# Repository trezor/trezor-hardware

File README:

Hardware design of TREZOR

https://trezor.io/

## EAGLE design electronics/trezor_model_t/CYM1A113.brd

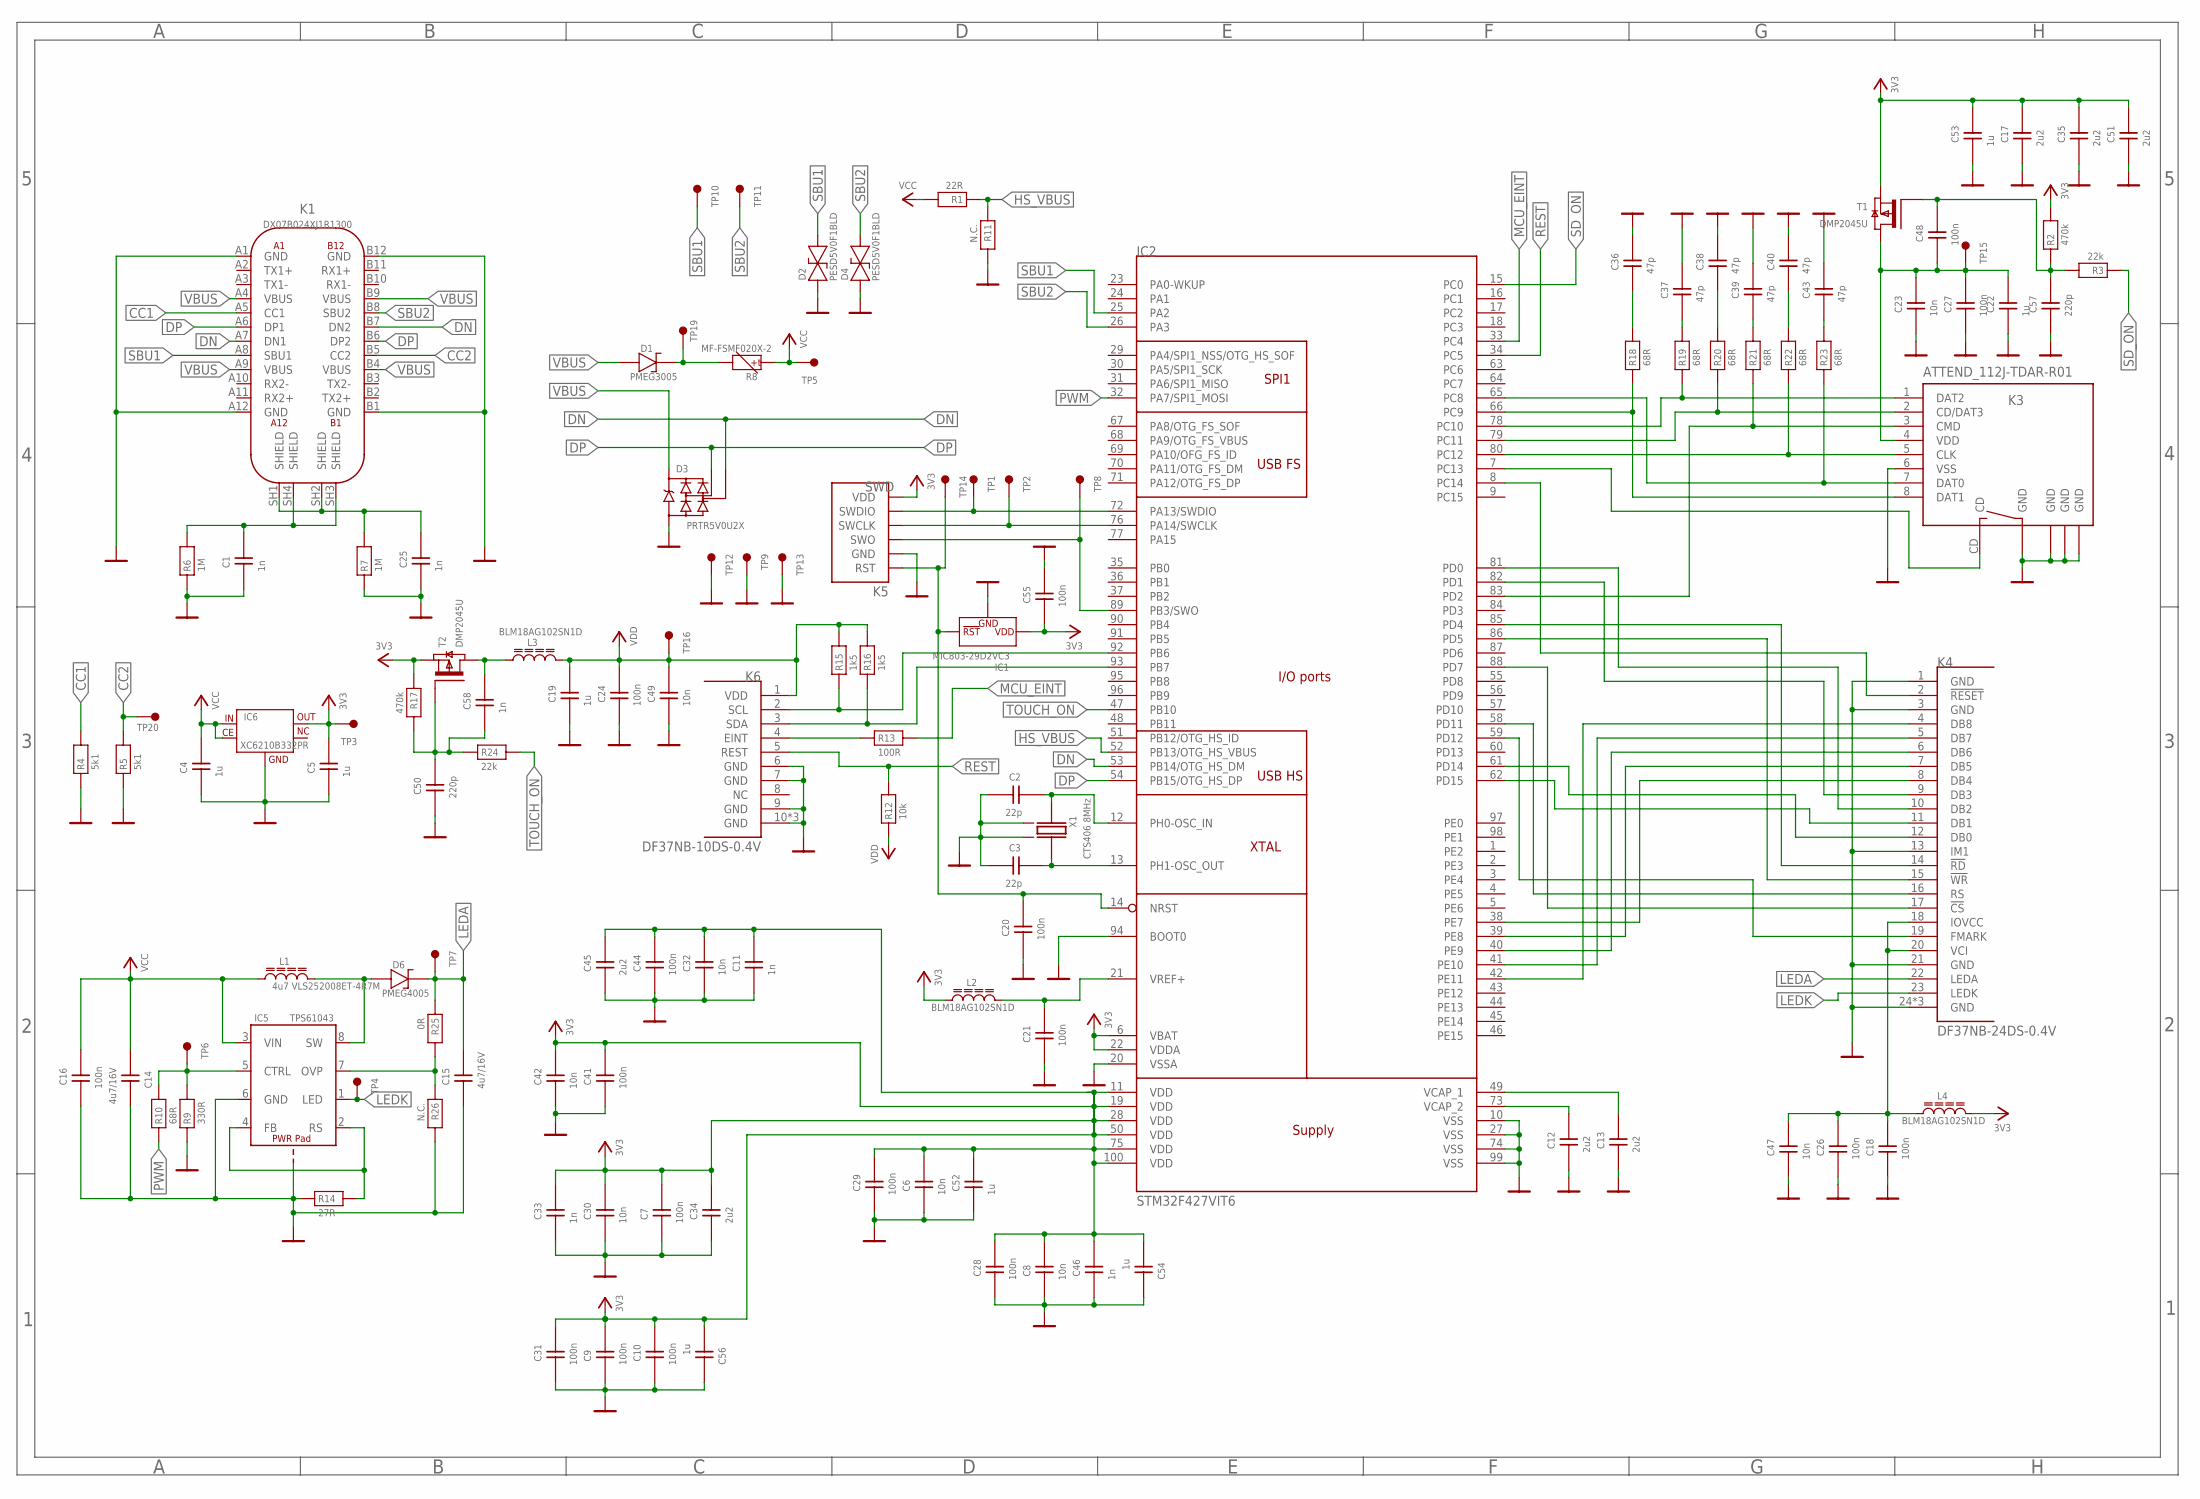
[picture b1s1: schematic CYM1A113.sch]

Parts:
C1, C11, C25, C33, C46, C58: 1n; 0402
C2, C3: 22p; 0402
C4, C19, C22, C52, C53, C54, C56: 1u; 0603_REFLOW
C5: 1u; 0603
C6, C8, C23, C30, C32, C42, C47, C49: 10n; 0402
C7, C9, C10, C16, C18, C20, C21, C24, C26, C27, C28, C29, C31, C41, C44, C48, C55: 100n; 0402
C12, C13, C17, C34, C35, C45, C51: 2u2; 0805_REFLOW
C14, C15: 4u7/16V; 0805_REFLOW
C36, C37, C38, C39, C40, C43: 47p; 0402
C50, C57: 220p; 0402
D1: PMEG3005; SOD323F
D2, D4: PESD5V0F1BLD; SOD882D
D3: PRTR5V0U2X; SOT143B_REFLOW
D6: PMEG4005; SOD323F
IC1: MIC803-29D2VC3; SOT23_MEDIUM_SIZE
IC2: STM32F427VIT6; LQFP100_NO_CENTER_NO_TDOCU
IC5: TPS61043; WSON-8_3X3MM
IC6: XC6210B332PR; SOT89-5
K1: DX07B024XJ1R1300; USB_C_JAE_DX07B024XJ1
K3: ATTEND_112J-TDAR-R01; ATTEND_112J-TXAR-R01_SMALL
K4: DF37NB-24DS-0.4V
K5: SWD
K6: DF37NB-10DS-0.4V
L1: 4u7 VLS252008ET-4R7M; L_2.5X2.0
L2, L3, L4: BLM18AG102SN1D; 0603_REFLOW
R1: 22R; 0402
R2, R17: 470k; 0402
R3, R24: 22k; 0402
R4, R5: 5k1; 0402
R6, R7: 1M; 0402
R8: MF-FSMF020X-2; 0603
R9: 330R; 0402
R10, R18, R19, R20, R21, R22, R23: 68R; 0402
R11, R26: N.C.; 0402
R12: 10k; 0402
R13: 100R; 0402
R14: 27R; 0402
R15, R16: 1k5; 0402
R25: 0R; 0402
T1, T2: DMP2045U; SOT23_REFLOW
TP1, TP2, TP4, TP6, TP7, TP8, TP9, TP12, TP13, TP14, TP15, TP16: MB_1.27; MB1.27
TP3, TP5, TP10, TP11: MB_1.50; MB1.5
TP19, TP20: MB_1.00
X1: CTS406 8MHz; X6,0X3,5

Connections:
CC1: K1.A5 (CC1), R4.P$2 (2)
CC2: K1.B5 (CC2), R5.P$2 (2), TP20.1
CTRL: IC5.5 (CTRL), R9.P$2 (2), R10.P$2 (2), TP6.1
DISP_!CS: IC2.88 (PD7), K4.17 (!CS)
DISP_!RD: IC2.85 (PD4), K4.14 (!RD)
DISP_!RESET: IC2.8 (PC14), K4.2 (!RESET)
DISP_!WR: IC2.86 (PD5), K4.15 (!WR)
DISP_DB0: IC2.61 (PD14), K4.12 (DB0)
DISP_DB1: IC2.62 (PD15), K4.11 (DB1)
DISP_DB2: IC2.81 (PD0), K4.10 (DB2)
DISP_DB3: IC2.82 (PD1), K4.9 (DB3)
DISP_DB4: IC2.38 (PE7), K4.8 (DB4)
DISP_DB5: IC2.39 (PE8), K4.7 (DB5)
DISP_DB6: IC2.40 (PE9), K4.6 (DB6)
DISP_DB7: IC2.41 (PE10), K4.5 (DB7)
DISP_DB8: IC2.42 (PE11), K4.4 (DB8)
DISP_FMARK: IC2.59 (PD12), K4.19 (FMARK)
DISP_RS: IC2.58 (PD11), K4.16 (RS)
DISP_VCC: C18.P$2 (2), C26.P$2 (2), C47.P$2 (2), K4.18 (IOVCC), K4.20 (VCI), L4.1
DN: D3.3 (I/O2), IC2.53 (PB14/OTG_HS_DM), K1.A7 (DN1), K1.B7 (DN2)
DP: D3.2 (I/O1), IC2.54 (PB15/OTG_HS_DP), K1.A6 (DP1), K1.B6 (DP2)
EINT: K6.4 (EINT), R13.P$1 (1)
FB_RS: IC5.2 (RS), IC5.4 (FB), R14.P$2 (2)
GND: C1.P$1 (1), C2.P$1 (1), C3.P$1 (1), C4.1, C5.1, C6.P$1 (1), C7.P$1 (1), C8.P$1 (1), C9.P$1 (1), C10.P$1 (1), C11.P$1 (1), C12.1, C13.1, C14.2, C15.1, C16.P$1 (1), C17.1, C18.P$1 (1), C19.1, C20.P$1 (1), C21.P$1 (1), C22.1, C23.P$1 (1), C24.P$1 (1), C25.P$1 (1), C26.P$1 (1), C27.P$1 (1), C28.P$1 (1), C29.P$1 (1), C30.P$1 (1), C31.P$1 (1), C32.P$1 (1), C33.P$1 (1), C34.1, C35.1, C36.P$2 (2), C37.P$2 (2), C38.P$2 (2), C39.P$2 (2), C40.P$2 (2), C41.P$1 (1), C42.P$1 (1), C43.P$2 (2), C44.P$1 (1), C45.1, C46.P$1 (1), C47.P$1 (1), C49.P$1 (1), C50.P$1 (1), C51.1, C52.1, C53.1, C54.2, C55.P$2 (2), C56.2, C57.P$1 (1), D2.1, D3.1 (GND), D4.1, IC1.1 (GND), IC2.10 (VSS), IC2.20 (VSSA), IC2.27 (VSS), IC2.74 (VSS), IC2.94 (BOOT0), IC2.99 (VSS), IC5.6 (GND), IC5.EP, IC5.EP$1 (EP), IC5.EP$2 (EP), IC5.EP$3 (EP), IC5.EP$4 (EP), IC6.2 (GND), K1.A1 (GND), K1.A12 (GND), K1.B1 (GND), K1.B12 (GND), K3.6 (VSS), K3.GND@1 (GND), K3.GND@2 (GND), K3.GND@3 (GND), K3.GND@4 (GND), K4.1 (GND), K4.3 (GND), K4.13 (IM1), K4.21 (GND), K4.24 (GND), K4.25 (GND), K4.26 (GND), K5.GND, K6.6 (GND), K6.7 (GND), K6.9 (GND), K6.10 (GND), K6.11 (GND), K6.12 (GND), R4.P$1 (1), R5.P$1 (1), R6.P$1 (1), R7.P$1 (1), R9.P$1 (1), R11.P$2 (2), R14.P$1 (1), R26.P$2 (2), TP9.1, TP12.1, TP13.1, X1.2 (GND1), X1.4 (GND2)
HS_VBUS: IC2.52 (PB13/OTG_HS_VBUS), R1.P$1 (1), R11.P$1 (1)
LEDA: C15.2, D6.K (2), K4.22 (LEDA), R25.P$1 (1), TP7.1
LEDK: IC5.1 (LED), K4.23 (LEDK), TP4.1
MCU_EINT: IC2.33 (PC4), R13.P$2 (2)
unnamed: C58.P$2 (2), L3.1, T2.3 (D)
unnamed: C1.P$2 (2), K1.SH3 (SHIELD), K1.SH4 (SHIELD), R6.P$2 (2)
unnamed: C25.P$2 (2), K1.SH1 (SHIELD), K1.SH2 (SHIELD), R7.P$2 (2)
unnamed: C36.P$1 (1), R18.P$2 (2)
unnamed: C37.P$1 (1), R19.P$2 (2)
unnamed: C38.P$1 (1), R20.P$2 (2)
unnamed: C39.P$1 (1), R21.P$2 (2)
unnamed: C40.P$1 (1), R22.P$2 (2)
unnamed: C43.P$1 (1), R23.P$2 (2)
unnamed: C22.2, C23.P$2 (2), C27.P$2 (2), C48.P$1 (1), K3.4 (VDD), T1.3 (D), TP15.1
unnamed: C2.P$2 (2), IC2.12 (PH0-OSC_IN), X1.1
unnamed: C3.P$2 (2), IC2.13 (PH1-OSC_OUT), X1.3 (2)
unnamed: C48.P$2 (2), C57.P$2 (2), R2.P$1 (1), R3.P$2 (2), T1.2 (G)
unnamed: D1.K (2), R8.2, TP19.1
unnamed: C12.2, IC2.73 (VCAP_2)
unnamed: C13.2, IC2.49 (VCAP_1)
unnamed: C50.P$2 (2), C58.P$1 (1), R17.P$2 (2), R24.P$1 (1), T2.2 (G)
OVP: IC5.7 (OVP), R25.P$2 (2), R26.P$1 (1)
PWM: IC2.32 (PA7/SPI1_MOSI), R10.P$1 (1)
REST: IC2.34 (PC5), K6.5 (REST), R12.P$2 (2)
RST: C20.P$2 (2), IC1.2 (RES), IC2.14 (NRST), K5.RST, TP14.1
SBU1: D2.2, IC2.25 (PA2), K1.A8 (SBU1), TP10.1
SBU2: D4.2, IC2.26 (PA3), K1.B8 (SBU2), TP11.1
SCL: IC2.92 (PB6), K6.2 (SCL), R15.P$1 (1)
SDA: IC2.93 (PB7), K6.3 (SDA), R16.P$1 (1)
SD_CD: IC2.7 (PC13), K3.CD
SD_CLK: IC2.80 (PC12), K3.5 (CLK), R22.P$1 (1)
SD_CMD: IC2.83 (PD2), K3.3 (CMD), R21.P$1 (1)
SD_DAT0: IC2.65 (PC8), K3.7 (DAT0), R23.P$1 (1)
SD_DAT1: IC2.66 (PC9), K3.8 (DAT1), R18.P$1 (1)
SD_DAT2: IC2.78 (PC10), K3.1 (DAT2), R19.P$1 (1)
SD_DAT3: IC2.79 (PC11), K3.2 (CD/DAT3), R20.P$1 (1)
SD_ON: IC2.15 (PC0), R3.P$1 (1)
SW: D6.A (1), IC5.8 (SW), L1.2
SWCLK: IC2.76 (PA14/SWCLK), K5.SWCLK, TP2.1
SWDIO: IC2.72 (PA13/SWDIO), K5.SWDIO, TP1.1
SWO: IC2.89 (PB3/SWO), K5.SWO, TP8.1
TOUCH_ON: IC2.47 (PB10), R24.P$2 (2)
VBUS: D1.A (1), D3.4 (VCC), K1.A4 (VBUS), K1.A9 (VBUS), K1.B4 (VBUS), K1.B9 (VBUS)
VCC: C4.2, C14.1, C16.P$2 (2), IC5.3 (VIN), IC6.1 (CE), IC6.4 (IN), L1.1, R1.P$2 (2), R8.1, TP5.1
VCC-2: C5.2, C6.P$2 (2), C7.P$2 (2), C8.P$2 (2), C9.P$2 (2), C10.P$2 (2), C11.P$2 (2), C17.2, C28.P$2 (2), C29.P$2 (2), C30.P$2 (2), C31.P$2 (2), C32.P$2 (2), C33.P$2 (2), C34.2, C35.2, C41.P$2 (2), C42.P$2 (2), C44.P$2 (2), C45.2, C46.P$2 (2), C51.2, C52.2, C53.2, C54.1, C55.P$1 (1), C56.1, IC1.3 (VDD), IC2.6 (VBAT), IC2.11 (VDD), IC2.19 (VDD), IC2.22 (VDDA), IC2.28 (VDD), IC2.50 (VDD), IC2.75 (VDD), IC2.100 (VDD), IC6.5 (OUT), K5.VCC (VDD), L2.1, L4.2, R2.P$2 (2), R17.P$1 (1), T1.1 (S), T2.1 (S), TP3.1
VDD: C19.2, C24.P$2 (2), C49.P$2 (2), K6.1 (VDD), L3.2, R12.P$1 (1), R15.P$2 (2), R16.P$2 (2), TP16.1
VREF+: C21.P$2 (2), IC2.21 (VREF+), L2.2

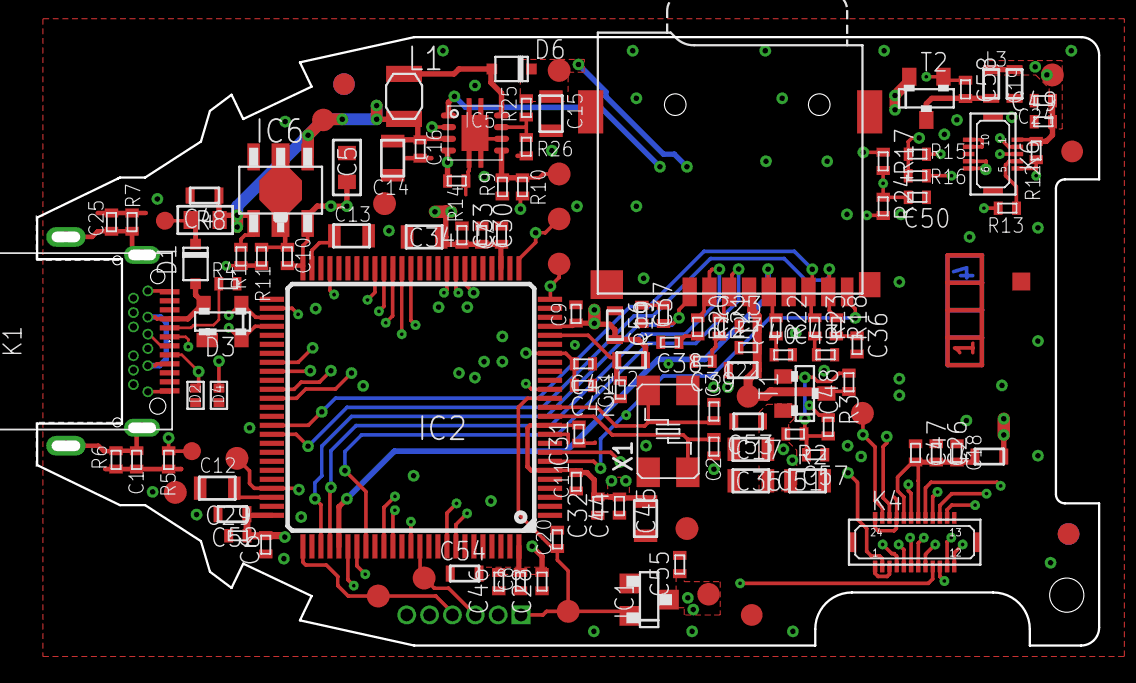
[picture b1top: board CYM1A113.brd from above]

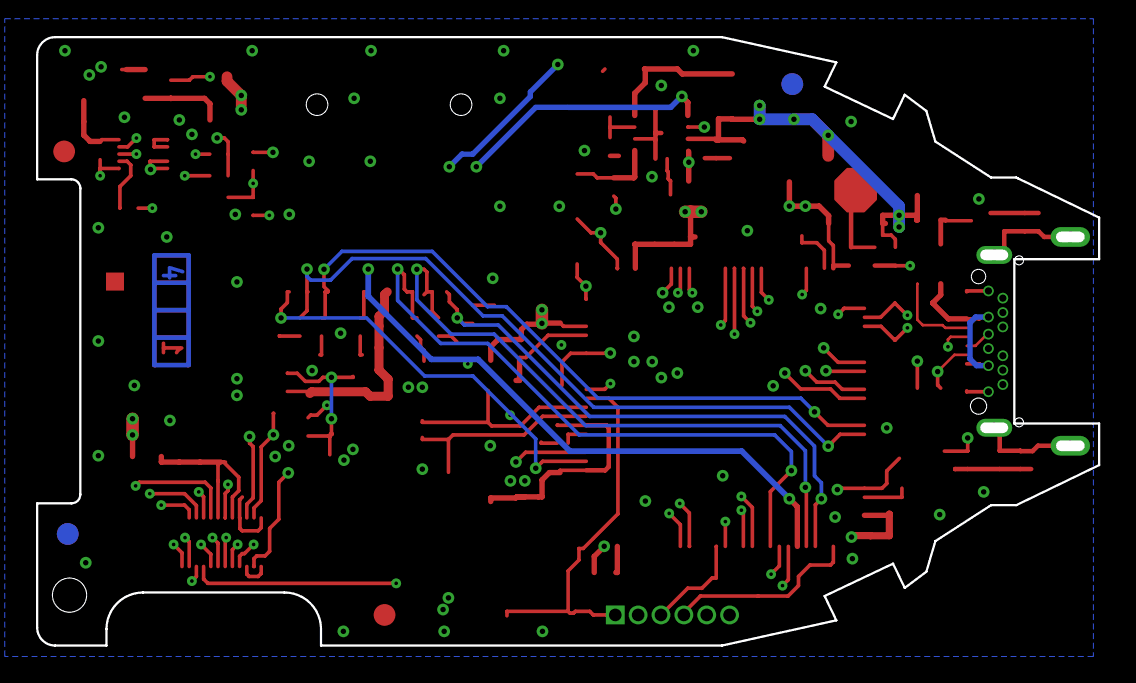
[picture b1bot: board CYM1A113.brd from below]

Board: 4 copper layers, 59.0 x 33.8 mm, 132 parts (2 on the bottom side), 71 nets.

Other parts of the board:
U$45, U$46, U$48, U$49, U$56, U$57: CENTR
U$47: BADMARK
U$53: RAM_BRD_ENG
U$54: LAYER_STACK_4_LAYERS

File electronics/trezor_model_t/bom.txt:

Part Value                Device                                  Package
C1   1n/50V               C_0402                                  0402
C2   22p                  C_0402                                  0402
C3   22p                  C_0402                                  0402
C4   1u                   C_0603                                  0603
C5   1u                   C_0603                                  0603
C6   10n                  C_0402                                  0402
C7   100n                 C_0402                                  0402
C8   10n                  C_0402                                  0402
C9   100n                 C_0402                                  0402
C10  100n                 C_0402                                  0402
C11  1n                   C_0402                                  0402
C12  2u2                  C_0805                                  0805
C13  2u2                  C_0805                                  0805
C14  4u7/16V              C_0805                                  0805
C15  4u7/16V              C_0805                                  0805
C16  100n                 C_0402                                  0402
C17  2u2                  C_0805                                  0805
C18  100n                 C_0402                                  0402
C19  1u                   C_0603                                  0603
C20  100n                 C_0402                                  0402
C21  100n                 C_0402                                  0402
C22  1u                   C_0603                                  0603
C23  10n                  C_0402                                  0402
C24  100n                 C_0402                                  0402
C25  1n/50V               C_0402                                  0402
C26  100n                 C_0402                                  0402
C27  100n                 C_0402                                  0402
C28  100n                 C_0402                                  0402
C29  100n                 C_0402                                  0402
C30  10n                  C_0402                                  0402
C31  100n                 C_0402                                  0402
C32  10n                  C_0402                                  0402
C33  1n                   C_0402                                  0402
C34  2u2                  C_0805                                  0805
C35  2u2                  C_0805                                  0805
C36  47p                  C_0402                                  0402
C37  47p                  C_0402                                  0402
C38  47p                  C_0402                                  0402
C39  47p                  C_0402                                  0402
C40  47p                  C_0402                                  0402
C41  100n                 C_0402                                  0402
C42  10n                  C_0402                                  0402
C43  47p                  C_0402                                  0402
C44  100n                 C_0402                                  0402
C45  2u2                  C_0805                                  0805
C46  1n                   C_0402                                  0402
C47  10n                  C_0402                                  0402
C48  100n                 C_0402                                  0402
C49  10n                  C_0402                                  0402
C50  220p                 C_0402                                  0402
C51  2u2                  C_0805                                  0805
C52  1u                   C_0603                                  0603
C53  1u                   C_0603                                  0603
C54  1u                   C_0603                                  0603
C55  100n                 C_0402                                  0402
C56  1u                   C_0603                                  0603
C57  220p                 C_0402                                  0402
C58  1n                   C_0402                                  0402
D1   PMEG3005EJ           DS_SOD323F                              SOD323F
D2   PESD5V0F1BLD         D_TRANSIL_BI_SOD882D                    SOD882D
D3   PRTR5V0U2X           PRTR5V0_SOT143B                         SOT143B
D4   PESD5V0F1BLD         D_TRANSIL_BI_SOD882D                    SOD882D
D6   PMEG4005EJ           DS_SOD323F                              SOD323F
IC1  MIC803-30D2VC3                                               SC70-3
IC2  STM32F427VIT6        STM32F427_LQFP100                       LQFP100_NO_CENTER_NO_TDOCU
IC5  TPS61043             TP6104X_WSON-8_3X3MM                    WSON-8_3X3MM
IC6  XC6210B332PR         XC6210B_SOT89-5                         SOT89-5
K1   DX07B024XJ1R1300     USB-C_JAE_DX07B024XJ1                   USB_C_JAE_DX07B024XJ1
K3   ATTEND_112J-TDAR-R01 KON_µSD_CARD_ATTEND_112J_TXAR_R01_SMALL ATTEND_112J-TXAR-R01_SMALL
K4   DF37NB-24DS-0.4V     DISPLEJ_154A2411CTP01                   DF37NB-24DS-0.4V
K5   SWD                  SWD                                     SWD
K6   DF37NB-10DS-0.4V     DISPLEJ_154A2411CTP01_TOUCH             DF37NB-10DS-0.4V
L1   4u7 VLS252008ET-4R7M L_2.5X2.0                               L_2.5X2.0
L2   BLM18AG601SN1D       L_0603                                  0603
L3   BLM18AG601SN1D       L_0603                                  0603
L4   BLM18AG601SN1D       L_0603                                  0603
LCD1                      LCD_DISPLEJ                             LCD
R1   22R                  R_0402                                  0402
R2   470k                 R_0402                                  0402
R3   22k                  R_0402                                  0402
R4   5k1                  R_0402                                  0402
R5   5k1                  R_0402                                  0402
R6   1M                   R_0402                                  0402
R7   1M                   R_0402                                  0402
R8   MF-FSMF020X-2        POLYSWITCH_0603                         0603
R9   330R                 R_0402                                  0402
R10  68R                  R_0402                                  0402
R11  N.C.                 R_0402                                  0402
R12  10k                  R_0402                                  0402
R13  100R                 R_0402                                  0402
R14  27R                  R_0402                                  0402
R15  1k5                  R_0402                                  0402
R16  1k5                  R_0402                                  0402
R17  470k                 R_0402                                  0402
R18  68R                  R_0402                                  0402
R19  68R                  R_0402                                  0402
R20  68R                  R_0402                                  0402
R21  68R                  R_0402                                  0402
R22  68R                  R_0402                                  0402
R23  68R                  R_0402                                  0402
R24  22k                  R_0402                                  0402
R25  0R                   R_0402                                  0402
R26  N.C.                 R_0402                                  0402
T1   DMP2045U                                                     SOT-23
T2   DMP2045U                                                     SOT-23
X1   CTS406 8MHz          X_4V_6,0X3,5                            X6,0X3,5

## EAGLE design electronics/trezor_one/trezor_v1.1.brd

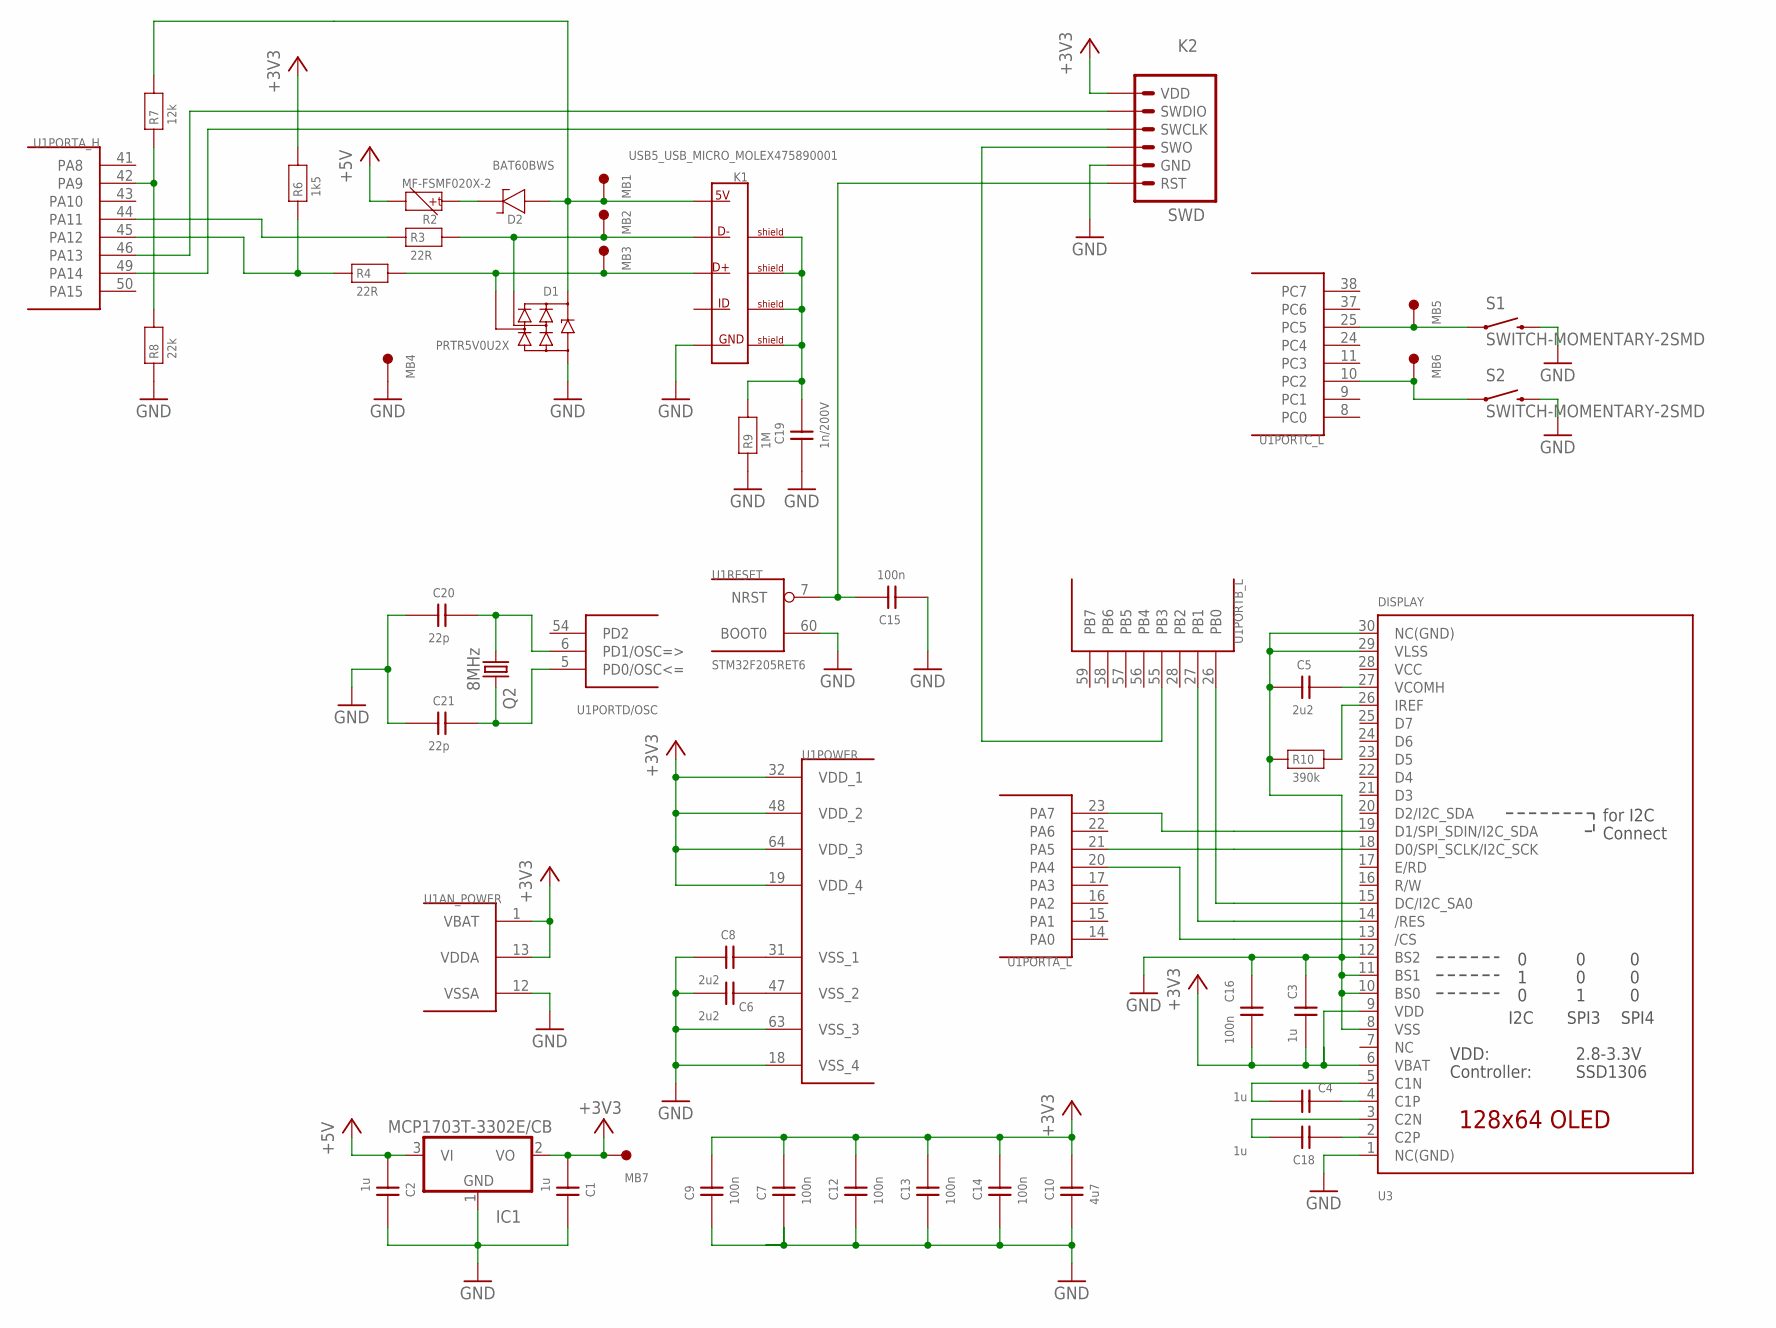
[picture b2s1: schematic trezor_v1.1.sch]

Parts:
C1, C2, C3, C4, C18: 1u; 0402
C5: 2u2; 0603
C6, C8: 2u2; 0402
C7, C9, C12, C13, C14, C15, C16: 100n; 0402
C10: 4u7; 0603
C19: 1n/200V; 0603
C20, C21: 22p; 0402
D1: PRTR5V0U2X; SOT143B
D2: BAT60BWS; SOD323
IC1: MCP1703T-3302E/CB; SOT23
K1: USB5_USB_MICRO_MOLEX475890001; USB_MICRO-MOLEX475890001
K2: SWD
MB1, MB2, MB3, MB4, MB5, MB6, MB7: MB_1.50; MB1.5
Q2: 8MHz; CTS406
R2: MF-FSMF020X-2; 0603
R3, R4: 22R; 0402
R6: 1k5; 0402
R7: 12k; 0402
R8: 22k; 0402
R9: 1M; 0603
R10: 390k; 0402
S1, S2: SWITCH-MOMENTARY-2SMD; TACTILE_SWITCH_SMD
U1: STM32F205RET6; TQFP64
U3: DISPLAY; UG-2864HSWEG01_0.96IN_WRAPAROUND

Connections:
+3V3: C1.P$1 (1), C3.P$1 (1), C7.P$2 (2), C9.P$2 (2), C10.2, C12.P$2 (2), C13.P$2 (2), C14.P$2 (2), C16.P$1 (1), IC1.2 (VO), K2.6 (VDD), MB7.1, R6.P$2 (2), U1.1 (VBAT), U1.13 (VDDA), U1.19 (VDD_4), U1.32 (VDD_1), U1.48 (VDD_2), U1.64 (VDD_3), U3.6 (VBAT), U3.9 (VDD)
+5V: C2.P$1 (1), IC1.3 (VI), R2.2
GND: C1.P$2 (2), C2.P$2 (2), C3.P$2 (2), C5.1, C6.P$1 (1), C7.P$1 (1), C8.P$1 (1), C9.P$1 (1), C10.1, C12.P$1 (1), C13.P$1 (1), C14.P$1 (1), C15.P$1 (1), C16.P$2 (2), C19.1, C20.P$1 (1), C21.P$1 (1), D1.1 (GND), IC1.1 (GND), K1.5 (5_GND), K2.2 (GND), MB4.1, R8.P$1 (1), R9.1, R10.P$1 (1), S1.3 (2), S1.4 (2), S2.3 (2), S2.4 (2), U1.12 (VSSA), U1.18 (VSS_4), U1.60 (BOOT0), U1.63 (VSS_3), U3.1 (NC(GND)), U3.8 (VSS), U3.10 (BS0), U3.11 (BS1), U3.12 (BS2), U3.29 (VLSS), U3.30 (NC(GND))
unnamed: U1.23 (PA7), U3.19 (D1/SPI_SDIN/I2C_SDA)
unnamed: C15.P$2 (2), K2.1 (RST), U1.7 (NRST)
unnamed: U1.26 (PB0), U3.15 (DC/I2C_SA0)
unnamed: C8.P$2 (2), U1.31 (VSS_1)
unnamed: U1.21 (PA5), U3.18 (D0/SPI_SCLK/I2C_SCK)
unnamed: C5.2, U3.27 (VCOMH)
unnamed: U1.27 (PB1), U3.14 (/RES)
unnamed: C6.P$2 (2), U1.47 (VSS_2)
unnamed: R10.P$2 (2), U3.26 (IREF)
unnamed: C18.P$1 (1), U3.2 (C2P)
unnamed: C4.P$1 (1), U3.4 (C1P)
unnamed: C18.P$2 (2), U3.3 (C2N)
unnamed: C4.P$2 (2), U3.5 (C1N)
unnamed: K2.3 (SWO), U1.55 (PB3)
unnamed: K2.5 (SWDIO), U1.46 (PA13)
unnamed: U1.20 (PA4), U3.13 (/CS)
unnamed: K2.4 (SWCLK), U1.49 (PA14)
unnamed: R3.P$1 (1), U1.44 (PA11)
unnamed: MB5.1, S1.1, S1.2 (1), U1.25 (PC5)
unnamed: MB6.1, S2.1, S2.2 (1), U1.10 (PC2)
unnamed: D1.4 (VCC), D2.A (1), K1.1 (1_5V), MB1.1, R7.P$2 (2)
unnamed: D2.K (2), R2.1
unnamed: D1.2 (I/O1), K1.2 (2_D-), MB2.1, R3.P$2 (2)
unnamed: D1.3 (I/O2), K1.3 (3_D+), MB3.1, R4.P$2 (2)
unnamed: C19.2, K1.S1_BOT (SHIELD_1), K1.S1_TOP (SHIELD_1), K1.S2_BOT (SHIELD_2), K1.S2_TOP (SHIELD_2), K1.S3_BOT (SHIELD_3), K1.S3_TOP (SHIELD_3), K1.S4_BOT (SHIELD_4), K1.S4_TOP (SHIELD_4), K1.SA (SHIELD_1), K1.SB (SHIELD_2), R9.2
unnamed: R7.P$1 (1), R8.P$2 (2), U1.42 (PA9)
USB_D_P: R4.P$1 (1), R6.P$1 (1), U1.45 (PA12)
VCC: U3.28 (VCC)
XTAL1: C20.P$2 (2), Q2.1, U1.6 (PD1/OSC=>)
XTAL2: C21.P$2 (2), Q2.3 (2), U1.5 (PD0/OSC<=)

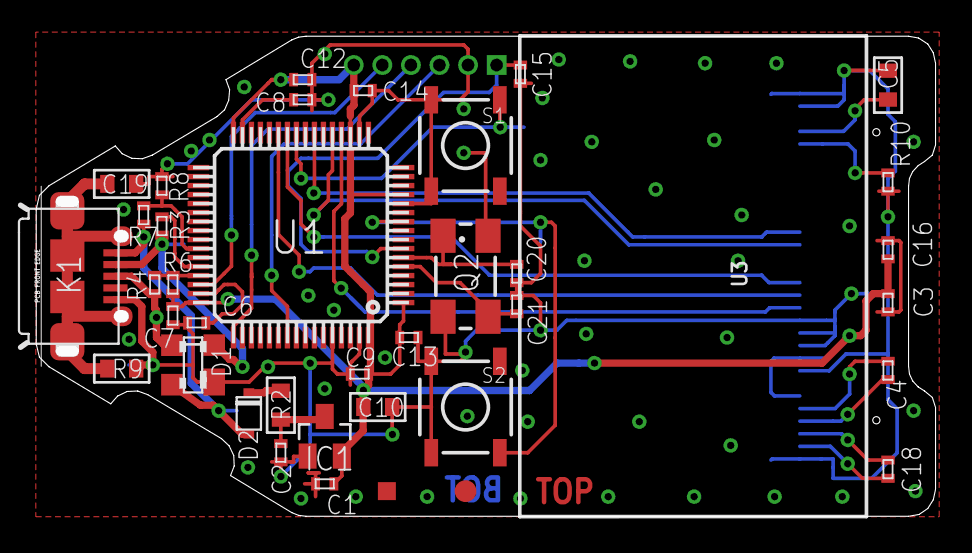
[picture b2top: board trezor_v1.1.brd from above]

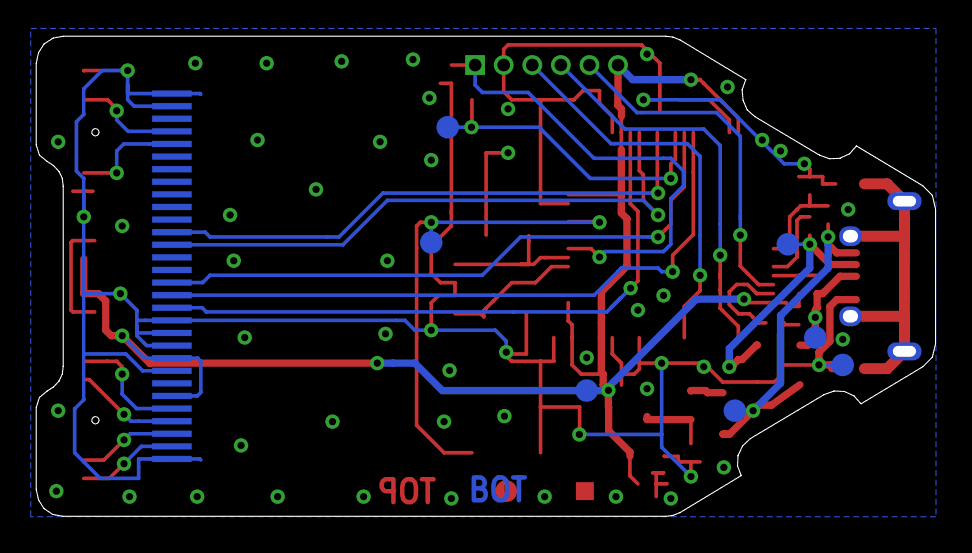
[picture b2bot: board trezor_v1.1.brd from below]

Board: 2 copper layers, 50.0 x 26.7 mm, 46 parts (7 on the bottom side), 32 nets.

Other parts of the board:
U$3: BADMARK
U$4: CENTR

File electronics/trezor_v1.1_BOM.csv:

Qty,Value,Device,Package,Parts,Description
7,100n,C_0402,402,"C7, C9, C12, C13, C14, C15, C16",
1,12k,R_0402,402,R7,
1,1M,R_0603,603,R9,
1,1k5,R_0402,402,R6,
1,1n/200V,C_0603,603,C19,
5,1u,C_0402,402,"C1, C2, C3, C4, C18",
2,22R,R_0402,402,"R3, R4",
1,22k,R_0402,402,R8,
2,22p,C_0402,402,"C20, C21",
2,2u2,C_0402,402,"C6, C8",
1,2u2,C_0603,603,C5,
1,390k,R_0402,402,R10,
1,4u7,C_0603,603,C10,
1,8MHz,CRYSTALCTS406,CTS406,Q2,CRYSTAL
1,BAT60BWS,DS_SOD323,SOD323,D2,
1,DISPLAY,"DISP_OLED_UG-2864HSWEG010.96"";UG-2864HSWEG01_0.96IN_WRAPAROUND""",U3,UG-2864HSWEG01 OLED display,
1,MCP1703T-3302E/CB,MCP1703CB,SOT23,IC1,"250 mA, 16V, Low Quiescent Current LDO Regulator"
1,MF-FSMF020X-2 ,POLYSWITCH_0603,603,R2,
1,PRTR5V0U2X,PRTR5V0_SOT143B,SOT143B,D1,
1,STM32F205RET6,STM32F10XRXT6,TQFP64,U1,STM32F101/103 64pin LQFP
1,SWD,SWD,SWD,K2,SWD
2,SWITCH-MOMENTARY-2SMD,SWITCH-MOMENTARY-2SMD,TACTILE_SWITCH_SMD,"S1, S2","Various NO switches- pushbuttons, reed, etc"
1,USB5_USB_MICRO_MOLEX475890001,USB5_USB_MICRO_MOLEX475890001,USB_MICRO-MOLEX475890001,K1,

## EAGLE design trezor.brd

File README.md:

# Hardware design of Trezor

https://trezor.io/

## Open Source Hardware

OSHWA UID: [CZ000005](https://certification.oshwa.org/cz000005.html)

The content of this repo is dual licensed under the following licenses:
* [GNU Affero General Public License v3](COPYING)
* [CERN Open Hardware Licence Version 2 - Strongly Reciprocal](LICENSE)

## Download

Download everything in a [single ZIP file](https://github.com/trezor/trezor-hardware/archive/master.zip).

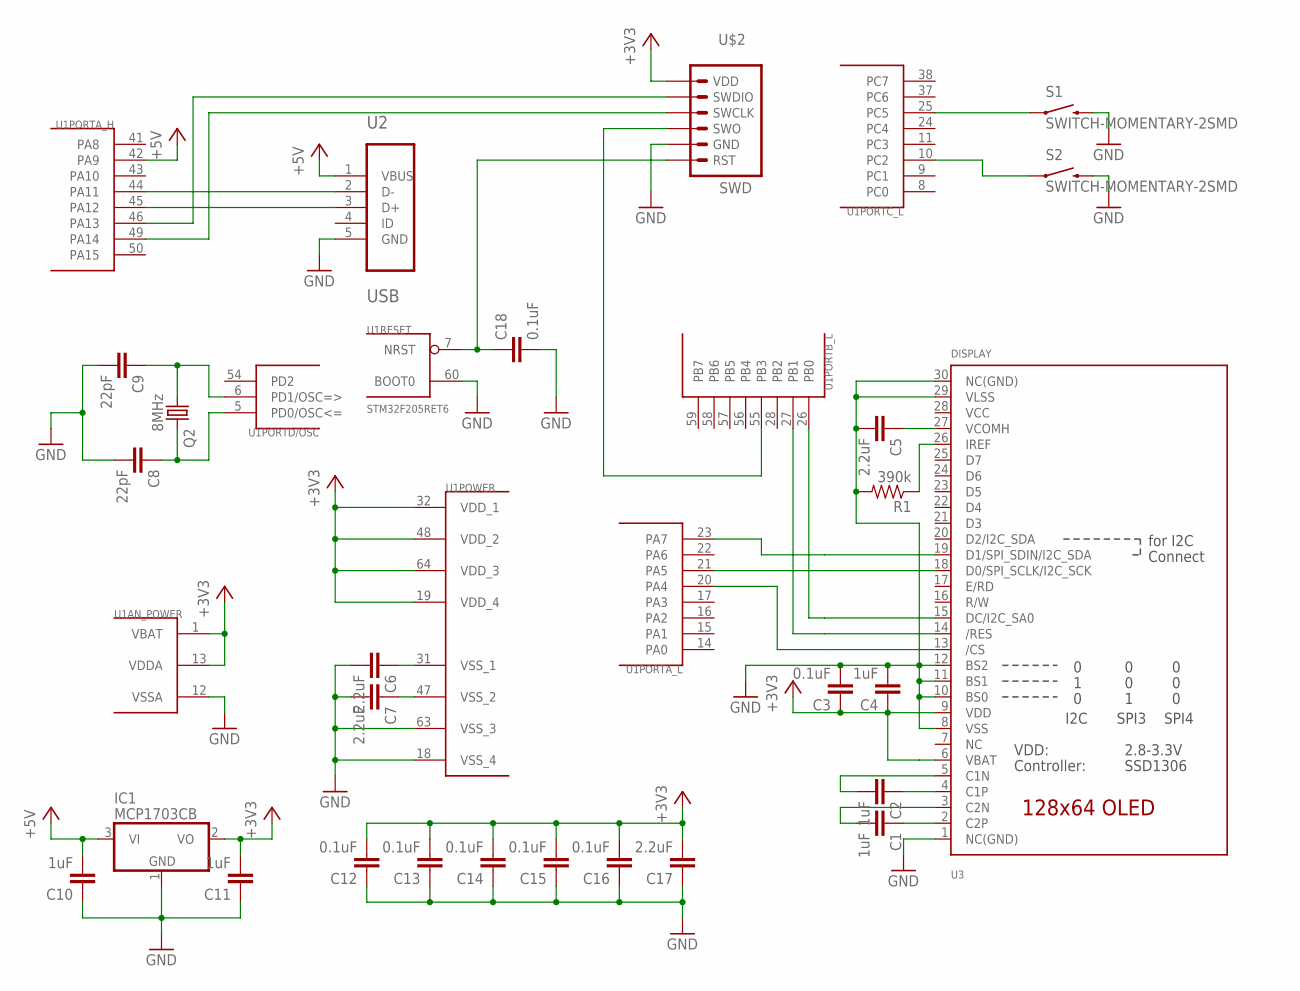
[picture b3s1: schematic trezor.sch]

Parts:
C1, C2, C4, C10, C11: 1uF; 0603-CAP
C3, C12, C13, C14, C15, C16, C18: 0.1uF; 0603-CAP
C5, C6, C7, C17: 2.2uF; 0603-CAP
C8, C9: 22pF; 0603-CAP
IC1: MCP1703CB; SOT23
Q2: 8MHz; CTS406
R1: 390k; 0603-RES
S1, S2: SWITCH-MOMENTARY-2SMD; TACTILE_SWITCH_SMD
U1: STM32F205RET6; TQFP64
U2: USB; MOLEX_47346-0001
U3: DISPLAY; UG-2864HSWEG01_0.96IN_WRAPAROUND
U$2: SWD

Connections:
+3V3: C3.1, C4.1, C11.2, C12.2, C13.2, C14.2, C15.2, C16.2, C17.2, IC1.2 (VO), U1.1 (VBAT), U1.13 (VDDA), U1.19 (VDD_4), U1.32 (VDD_1), U1.48 (VDD_2), U1.64 (VDD_3), U3.6 (VBAT), U3.9 (VDD), U$2.6 (VDD)
+5V: C10.2, IC1.3 (VI), U1.42 (PA9), U2.1 (VBUS)
GND: C3.2, C4.2, C5.2, C6.2, C7.2, C8.2, C9.2, C10.1, C11.1, C12.1, C13.1, C14.1, C15.1, C16.1, C17.1, C18.2, IC1.1 (GND), R1.2, S1.3 (2), S2.3 (2), U1.12 (VSSA), U1.18 (VSS_4), U1.60 (BOOT0), U1.63 (VSS_3), U2.5 (GND), U3.1 (NC(GND)), U3.8 (VSS), U3.10 (BS0), U3.11 (BS1), U3.12 (BS2), U3.29 (VLSS), U3.30 (NC(GND)), U$2.2 (GND)
unnamed: U1.23 (PA7), U3.19 (D1/SPI_SDIN/I2C_SDA)
unnamed: C18.1, U1.7 (NRST), U$2.1 (RST)
unnamed: U1.26 (PB0), U3.15 (DC/I2C_SA0)
unnamed: C6.1, U1.31 (VSS_1)
unnamed: U1.21 (PA5), U3.18 (D0/SPI_SCLK/I2C_SCK)
unnamed: C5.1, U3.27 (VCOMH)
unnamed: U1.27 (PB1), U3.14 (/RES)
unnamed: C7.1, U1.47 (VSS_2)
unnamed: R1.1, U3.26 (IREF)
unnamed: C1.1, U3.2 (C2P)
unnamed: C2.1, U3.4 (C1P)
unnamed: C1.2, U3.3 (C2N)
unnamed: C2.2, U3.5 (C1N)
unnamed: U1.55 (PB3), U$2.3 (SWO)
unnamed: U1.46 (PA13), U$2.5 (SWDIO)
unnamed: U1.20 (PA4), U3.13 (/CS)
unnamed: U1.49 (PA14), U$2.4 (SWCLK)
unnamed: S1.1, U1.25 (PC5)
unnamed: S2.1, U1.10 (PC2)
USB_D_N: U1.44 (PA11), U2.2 (D-)
USB_D_P: U1.45 (PA12), U2.3 (D+)
VCC: U3.28 (VCC)
XTAL1: C9.1, Q2.1, U1.6 (PD1/OSC=>)
XTAL2: C8.1, Q2.3 (2), U1.5 (PD0/OSC<=)

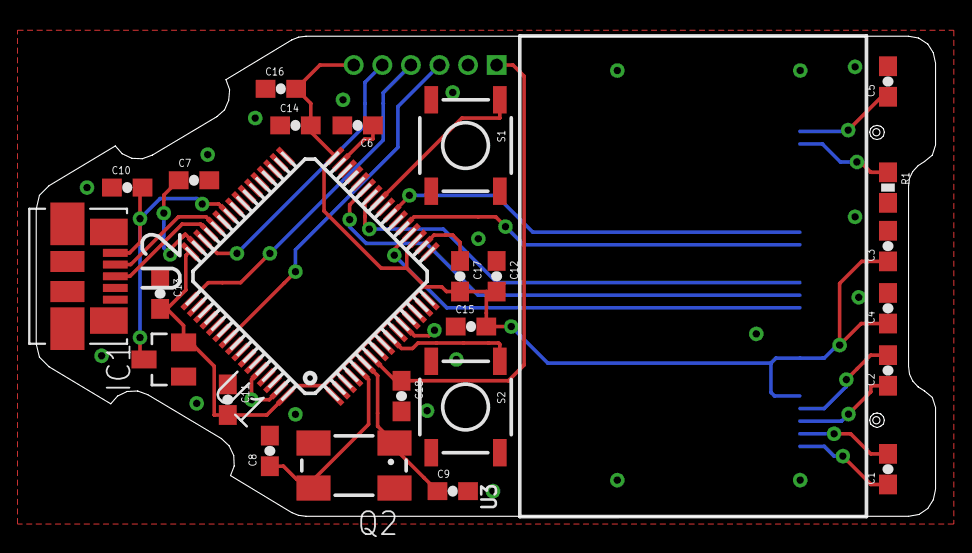
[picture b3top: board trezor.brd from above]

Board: 2 copper layers, 50.0 x 26.7 mm, 27 parts (0 on the bottom side), 26 nets.

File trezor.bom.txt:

Trezor
======

- 5x SMD 0603 Capacitor 1uF - C1, C2, C4, C10, C11
- 7x SMD 0603 Capacitor 0.1uF - C3, C12, C13, C14, C15, C16, C18
- 4x SMD 0603 Capacitor 2.2uF - C5, C6, C7, C17
- 2x SMD 0603 Capacitor 22pF - C8, C9

- 1x SMD 0603 Resistor 390k - R1

- 2x Microbuton P-B17310
  * http://www.gme.cz/mikrospinace-do-dps/p-b17310-p630-143/

- 1x Micro USB (type B) Receptacle Bottom
  * http://cz.farnell.com/molex/47346-0001/micro-usb-type-b-rece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

- 1x OLED display 128x64 UG-2864HSWEG01
  * http://www.wide.hk/products.php?product=128X64-OLED-LED-Disp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

- 1x STM32F205RE
  * http://www.st.com/web/catalog/mmc/FM141/SC1169/SS1575/LN1433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
  * http://cz.farnell.com/stmicroelectronics/stm32f205ret6/ic-mc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

- 1x MCP1703 Low Dropout Voltage Regulator
  * http://www.microchip.com/wwwproducts/Devices.aspx?dDocName=e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
  * http://cz.farnell.com/microchip/mcp1703t-3302e-cb/v-reg-ldo-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

- 1x ABMM2 8 MHz Crystal
  * http://cz.farnell.com/abracon/abmm2-8-000mhz-e2-t/crystal-8m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

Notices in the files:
parts and their libraries:
microbuilder: This work is placed in the public domain, and may be freely used for commercial and non-commercial work with the following conditions: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
SparkFun-Electromechanical: Licensing: CC v3.0 Share-Alike You are welcome to use this library for commercial purposes.
